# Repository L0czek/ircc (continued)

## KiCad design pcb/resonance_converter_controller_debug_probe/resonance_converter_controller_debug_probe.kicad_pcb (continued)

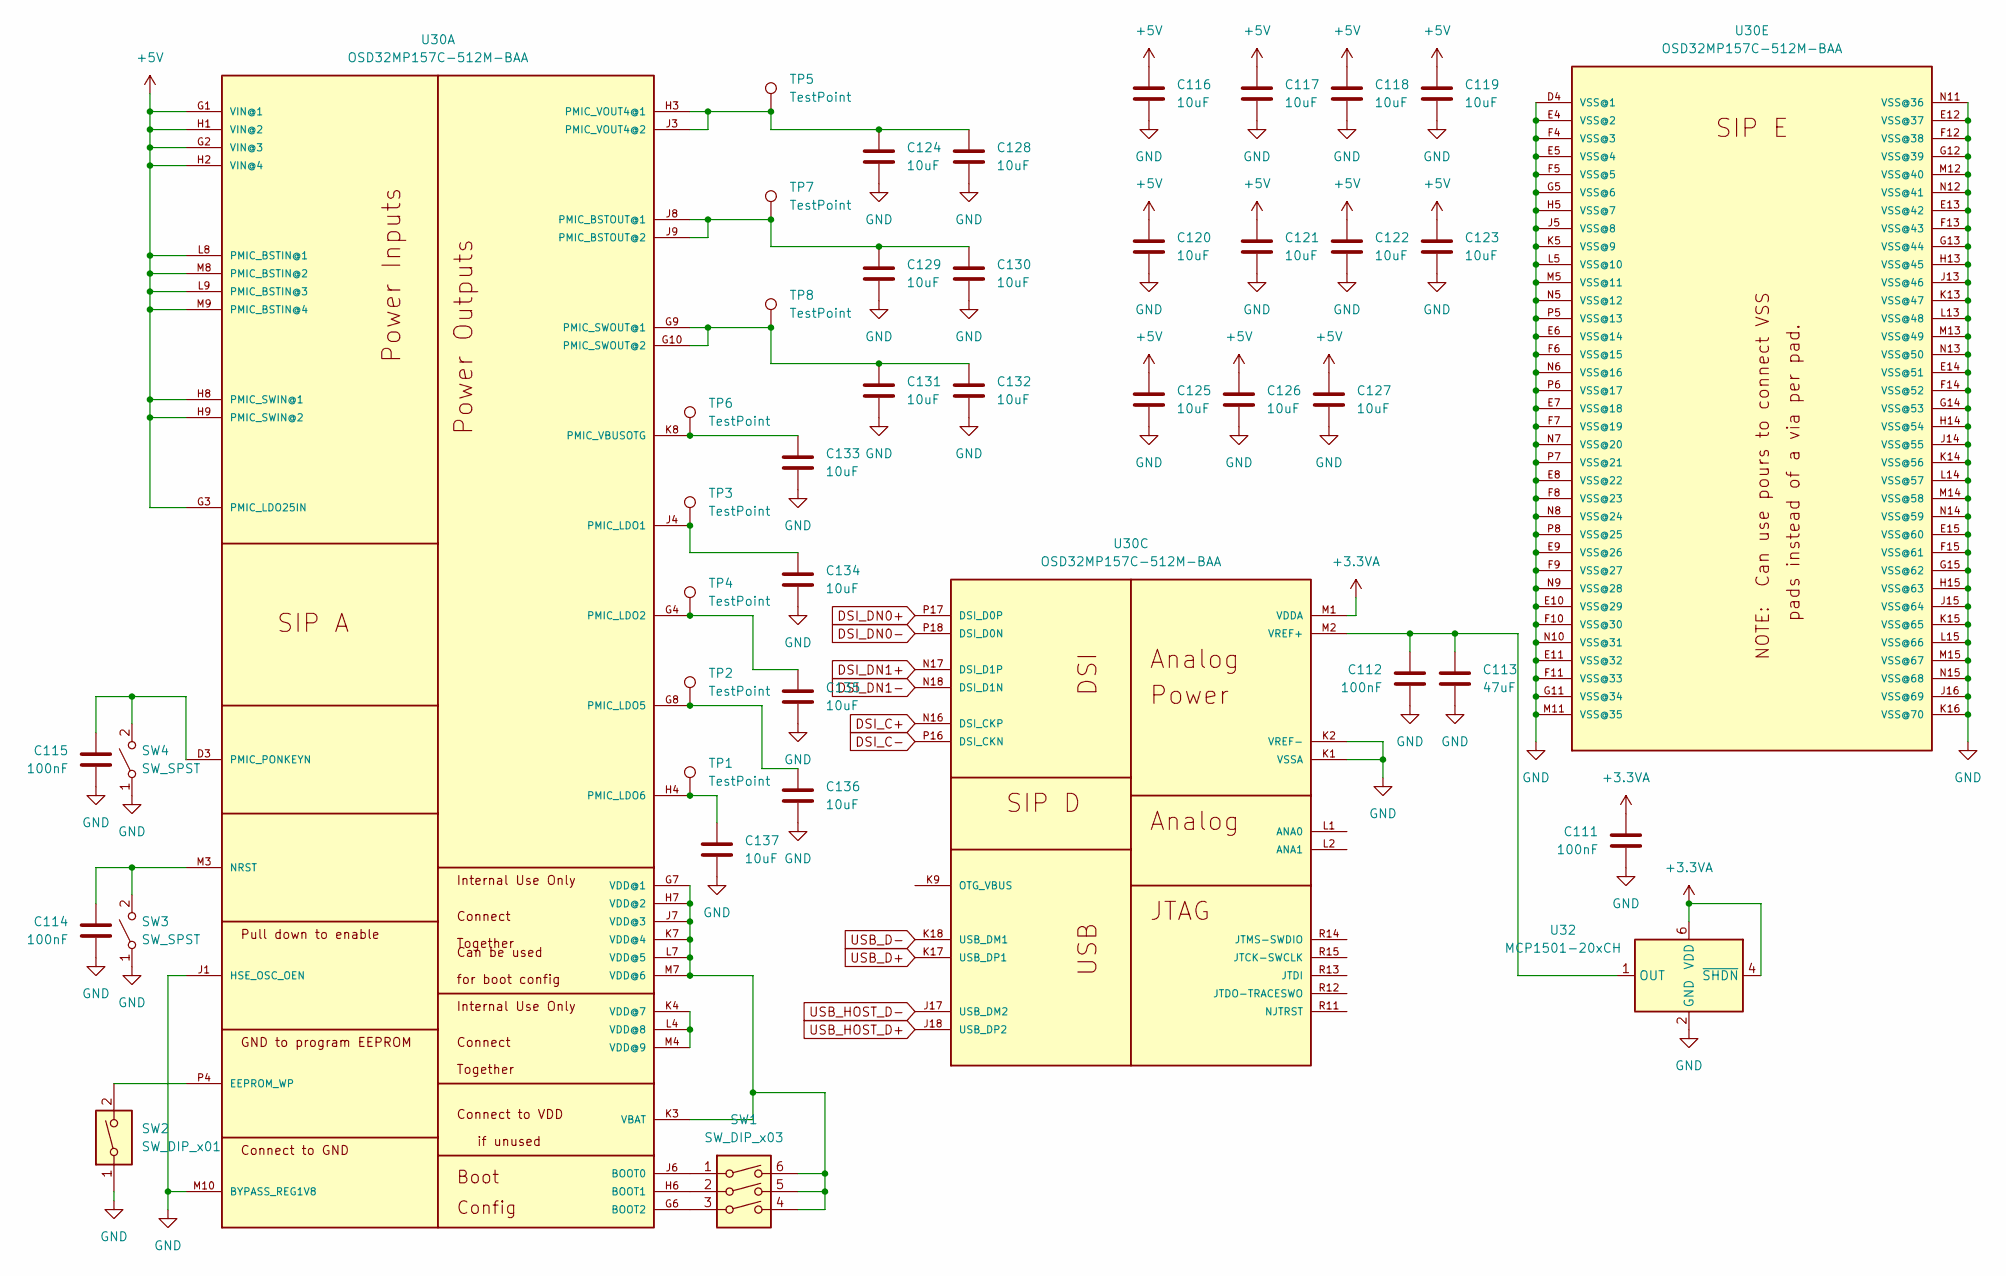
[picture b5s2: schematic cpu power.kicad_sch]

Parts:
C111, C112, C114, C115: 100nF; C_0402_1005Metric
C113: 47uF; C_1206_3216Metric
C116, C117, C118, C119, C120, C121, C122, C123, C124, C125, C126, C127, C128, C129, C130, C131, C132, C133, C134, C135, C136, C137: 10uF; C_0402_1005Metric
SW1: SW_DIP_x03; SW_DIP_SPSTx03_Slide_Omron_A6S-310x_W8.9mm_P2.54mm
SW2: SW_DIP_x01; SW_DIP_SPSTx01_Slide_Omron_A6S-110x_W8.9mm_P2.54mm
SW3, SW4: SW_SPST; SW_SPST_Omron_B3FS-100xP
TP1, TP2, TP3, TP4, TP5, TP6, TP7, TP8: TestPoint; TestPoint_Pad_D1.0mm
U30: OSD32MP157C-512M-BAA; OSD32MP15X-BGA-324
U32: MCP1501-20xCH; SOT-23-6

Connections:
+3.3VA: C111.1, U30.M1 (VDDA), U32.4 (~SHDN), U32.6 (VDD); also elsewhere on the board
+5V: C116.1, C117.1, C118.1, C119.1, C120.1, C121.1, C122.1, C123.1, C125.1, C126.1, C127.1, U30.G1 (VIN@1), U30.G2 (VIN@3), U30.G3 (PMIC_LDO25IN), U30.H1 (VIN@2), U30.H2 (VIN@4), U30.H8 (PMIC_SWIN@1), U30.H9 (PMIC_SWIN@2), U30.L8 (PMIC_BSTIN@1), U30.L9 (PMIC_BSTIN@3), U30.M8 (PMIC_BSTIN@2), U30.M9 (PMIC_BSTIN@4); also elsewhere on the board
DSI_C+: U30.N16 (DSI_CKP); also elsewhere on the board
DSI_C-: U30.P16 (DSI_CKN); also elsewhere on the board
DSI_DN0+: U30.P17 (DSI_D0P); also elsewhere on the board
DSI_DN0-: U30.P18 (DSI_D0N); also elsewhere on the board
DSI_DN1+: U30.N17 (DSI_D1P); also elsewhere on the board
DSI_DN1-: U30.N18 (DSI_D1N); also elsewhere on the board
GND: C111.2, C112.2, C113.2, C114.2, C115.2, C116.2, C117.2, C118.2, C119.2, C120.2, C121.2, C122.2, C123.2, C124.2, C125.2, C126.2, C127.2, C128.2, C129.2, C130.2, C131.2, C132.2, C133.2, C134.2, C135.2, C136.2, C137.2, SW2.1, SW3.1 (A), SW4.1 (A), U30.D4 (VSS@1), U30.E4 (VSS@2), U30.E5 (VSS@4), U30.E6 (VSS@14), U30.E7 (VSS@18), U30.E8 (VSS@22), U30.E9 (VSS@26), U30.E10 (VSS@29), U30.E11 (VSS@32), U30.E12 (VSS@37), U30.E13 (VSS@42), U30.E14 (VSS@51), U30.E15 (VSS@60), U30.F4 (VSS@3), U30.F5 (VSS@5), U30.F6 (VSS@15), U30.F7 (VSS@19), U30.F8 (VSS@23), U30.F9 (VSS@27), U30.F10 (VSS@30), U30.F11 (VSS@33), U30.F12 (VSS@38), U30.F13 (VSS@43), U30.F14 (VSS@52), U30.F15 (VSS@61), U30.G5 (VSS@6), U30.G11 (VSS@34), U30.G12 (VSS@39), U30.G13 (VSS@44), U30.G14 (VSS@53), U30.G15 (VSS@62), U30.H5 (VSS@7), U30.H13 (VSS@45), U30.H14 (VSS@54), U30.H15 (VSS@63), U30.J1 (HSE_OSC_OEN), U30.J5 (VSS@8), U30.J13 (VSS@46), U30.J14 (VSS@55), U30.J15 (VSS@64), U30.J16 (VSS@69), U30.K1 (VSSA), U30.K2 (VREF-), U30.K5 (VSS@9), U30.K13 (VSS@47), U30.K14 (VSS@56), U30.K15 (VSS@65), U30.K16 (VSS@70), U30.L5 (VSS@10), U30.L13 (VSS@48), U30.L14 (VSS@57), U30.L15 (VSS@66), U30.M5 (VSS@11), U30.M10 (BYPASS_REG1V8), U30.M11 (VSS@35), U30.M12 (VSS@40), U30.M13 (VSS@49), U30.M14 (VSS@58), U30.M15 (VSS@67), U30.N5 (VSS@12), U30.N6 (VSS@16), U30.N7 (VSS@20), U30.N8 (VSS@24), U30.N9 (VSS@28), U30.N10 (VSS@31), U30.N11 (VSS@36), U30.N12 (VSS@41), U30.N13 (VSS@50), U30.N14 (VSS@59), U30.N15 (VSS@68), U30.P5 (VSS@13), U30.P6 (VSS@17), U30.P7 (VSS@21), U30.P8 (VSS@25), U32.2 (GND), U32.3 (GND), U32.5 (GND); also elsewhere on the board
unnamed: C114.1, SW3.2 (B), U30.M3 (NRST)
unnamed: C115.1, SW4.2 (B), U30.D3 (PMIC_PONKEYN)
unnamed: SW1.1, U30.J6 (BOOT0)
unnamed: SW1.2, U30.H6 (BOOT1)
unnamed: SW1.3, U30.G6 (BOOT2)
unnamed: SW2.2, U30.P4 (EEPROM_WP)
unnamed: C129.1, C130.1, TP7.1, U30.J8 (PMIC_BSTOUT@1), U30.J9 (PMIC_BSTOUT@2)
unnamed: C134.1, TP3.1, U30.J4 (PMIC_LDO1)
unnamed: C135.1, TP4.1, U30.G4 (PMIC_LDO2)
unnamed: C136.1, TP2.1, U30.G8 (PMIC_LDO5)
unnamed: C137.1, TP1.1, U30.H4 (PMIC_LDO6)
unnamed: C131.1, C132.1, TP8.1, U30.G9 (PMIC_SWOUT@1), U30.G10 (PMIC_SWOUT@2)
unnamed: C133.1, TP6.1, U30.K8 (PMIC_VBUSOTG)
unnamed: C124.1, C128.1, TP5.1, U30.H3 (PMIC_VOUT4@1), U30.J3 (PMIC_VOUT4@2)
unnamed: SW1.4, SW1.5, SW1.6, U30.G7 (VDD@1), U30.H7 (VDD@2), U30.J7 (VDD@3), U30.K3 (VBAT), U30.K7 (VDD@4), U30.L7 (VDD@5), U30.M7 (VDD@6)
unnamed: U30.K4 (VDD@7), U30.L4 (VDD@8), U30.M4 (VDD@9)
unnamed: C112.1, C113.1, U30.M2 (VREF+), U32.1 (OUT)
USB_D+: U30.K17 (USB_DP1); also elsewhere on the board
USB_D-: U30.K18 (USB_DM1); also elsewhere on the board
USB_HOST_D+: U30.J18 (USB_DP2); also elsewhere on the board
USB_HOST_D-: U30.J17 (USB_DM2); also elsewhere on the board

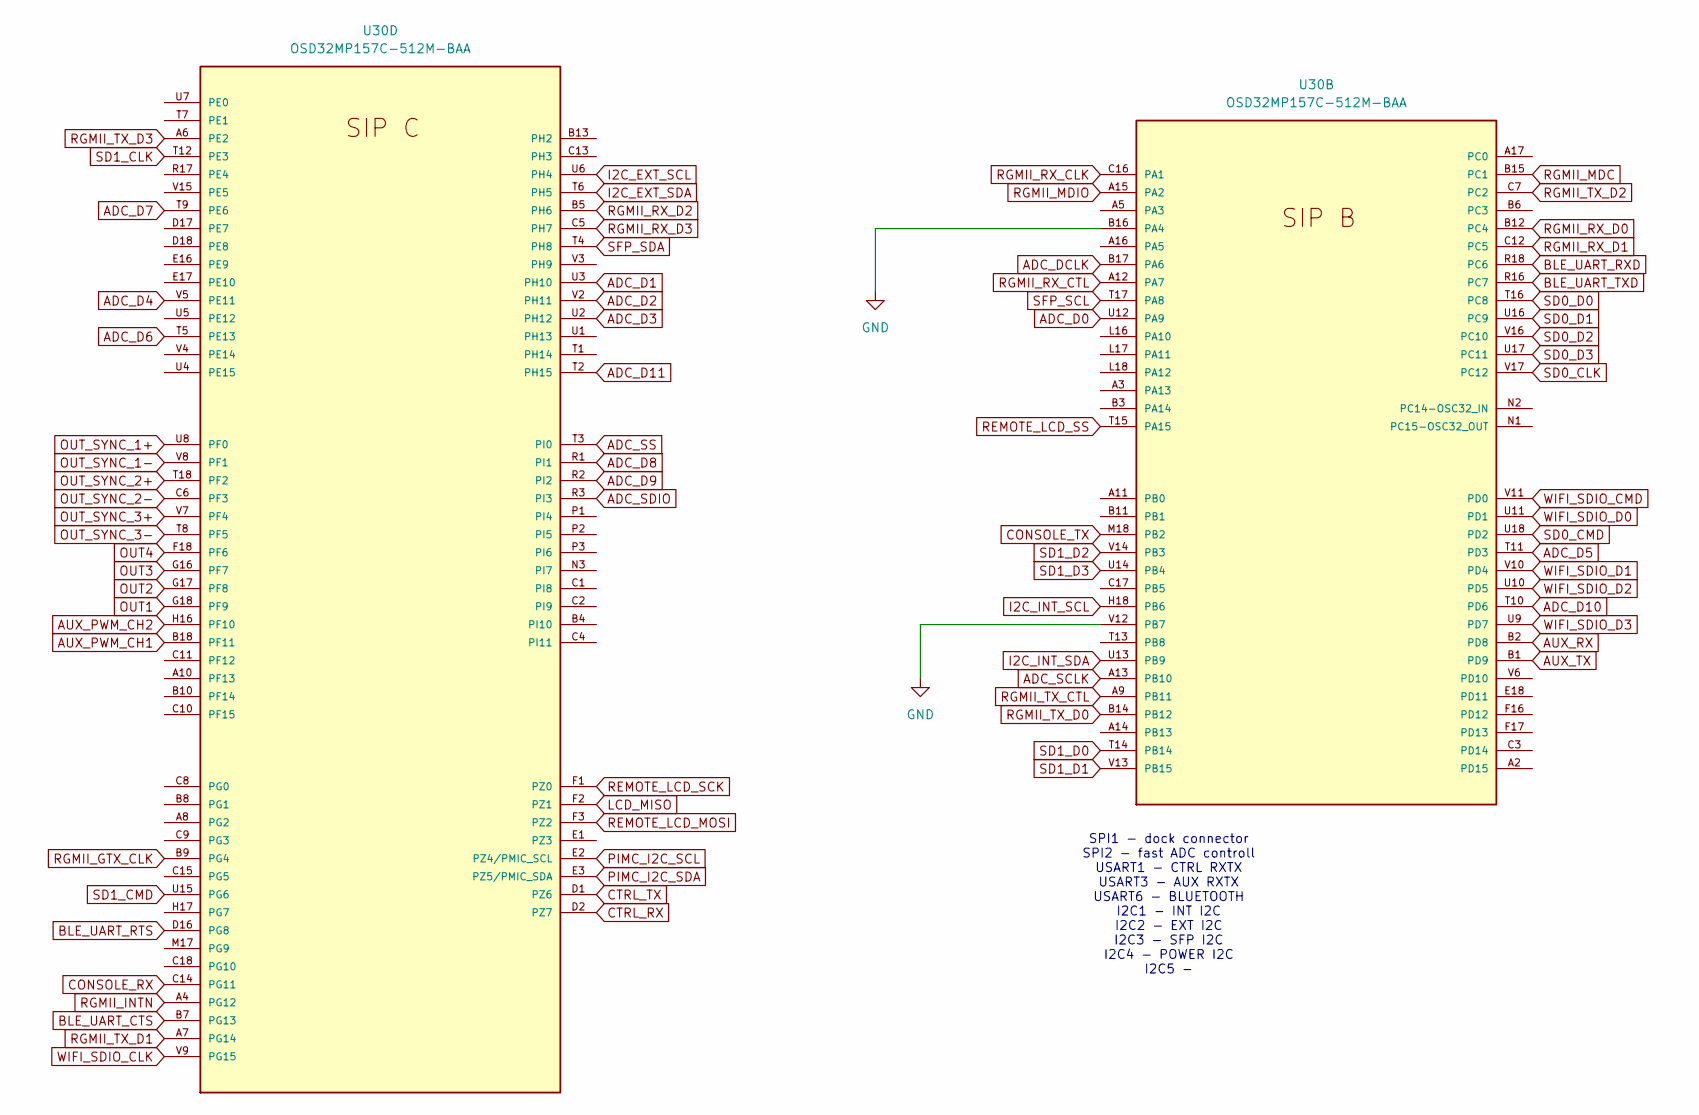
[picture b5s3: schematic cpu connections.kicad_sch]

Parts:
U30: OSD32MP157C-512M-BAA; OSD32MP15X-BGA-324

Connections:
ADC_D0: U30.U12 (PA9); also elsewhere on the board
ADC_D1: U30.U3 (PH10); also elsewhere on the board
ADC_D2: U30.V2 (PH11); also elsewhere on the board
ADC_D3: U30.U2 (PH12); also elsewhere on the board
ADC_D4: U30.V5 (PE11); also elsewhere on the board
ADC_D5: U30.T11 (PD3); also elsewhere on the board
ADC_D6: U30.T5 (PE13); also elsewhere on the board
ADC_D7: U30.T9 (PE6); also elsewhere on the board
ADC_D8: U30.R1 (PI1); also elsewhere on the board
ADC_D9: U30.R2 (PI2); also elsewhere on the board
ADC_D10: U30.T10 (PD6); also elsewhere on the board
ADC_D11: U30.T2 (PH15); also elsewhere on the board
ADC_DCLK: U30.B17 (PA6); also elsewhere on the board
ADC_SCLK: U30.A13 (PB10); also elsewhere on the board
ADC_SDIO: U30.R3 (PI3); also elsewhere on the board
ADC_SS: U30.T3 (PI0); also elsewhere on the board
AUX_PWM_CH1: U30.B18 (PF11); also elsewhere on the board
AUX_PWM_CH2: U30.H16 (PF10); also elsewhere on the board
AUX_RX: U30.B2 (PD8); also elsewhere on the board
AUX_TX: U30.B1 (PD9); also elsewhere on the board
BLE_UART_CTS: U30.B7 (PG13); also elsewhere on the board
BLE_UART_RTS: U30.D16 (PG8); also elsewhere on the board
BLE_UART_RXD: U30.R18 (PC6); also elsewhere on the board
BLE_UART_TXD: U30.R16 (PC7); also elsewhere on the board
CONSOLE_RX: U30.C14 (PG11); also elsewhere on the board
CONSOLE_TX: U30.M18 (PB2); also elsewhere on the board
CTRL_RX: U30.D2 (PZ7); also elsewhere on the board
CTRL_TX: U30.D1 (PZ6); also elsewhere on the board
GND: U30.B16 (PA4), U30.V12 (PB7); also elsewhere on the board
I2C_EXT_SCL: U30.U6 (PH4); also elsewhere on the board
I2C_EXT_SDA: U30.T6 (PH5); also elsewhere on the board
I2C_INT_SCL: U30.H18 (PB6); also elsewhere on the board
I2C_INT_SDA: U30.U13 (PB9); also elsewhere on the board
LCD_MISO: U30.F2 (PZ1)
OUT1: U30.G18 (PF9); also elsewhere on the board
OUT2: U30.G17 (PF8); also elsewhere on the board
OUT3: U30.G16 (PF7); also elsewhere on the board
OUT4: U30.F18 (PF6); also elsewhere on the board
OUT_SYNC_1+: U30.U8 (PF0); also elsewhere on the board
OUT_SYNC_1-: U30.V8 (PF1); also elsewhere on the board
OUT_SYNC_2+: U30.T18 (PF2); also elsewhere on the board
OUT_SYNC_2-: U30.C6 (PF3); also elsewhere on the board
OUT_SYNC_3+: U30.V7 (PF4); also elsewhere on the board
OUT_SYNC_3-: U30.T8 (PF5); also elsewhere on the board
PIMC_I2C_SCL: U30.E2 (PZ4/PMIC_SCL)
PIMC_I2C_SDA: U30.E3 (PZ5/PMIC_SDA)
REMOTE_LCD_MOSI: U30.F3 (PZ2)
REMOTE_LCD_SCK: U30.F1 (PZ0)
REMOTE_LCD_SS: U30.T15 (PA15)
RGMII_GTX_CLK: U30.B9 (PG4); also elsewhere on the board
RGMII_INTN: U30.A4 (PG12); also elsewhere on the board
RGMII_MDC: U30.B15 (PC1); also elsewhere on the board
RGMII_MDIO: U30.A15 (PA2); also elsewhere on the board
RGMII_RX_CLK: U30.C16 (PA1); also elsewhere on the board
RGMII_RX_CTL: U30.A12 (PA7); also elsewhere on the board
RGMII_RX_D0: U30.B12 (PC4); also elsewhere on the board
RGMII_RX_D1: U30.C12 (PC5); also elsewhere on the board
RGMII_RX_D2: U30.B5 (PH6); also elsewhere on the board
RGMII_RX_D3: U30.C5 (PH7); also elsewhere on the board
RGMII_TX_CTL: U30.A9 (PB11); also elsewhere on the board
RGMII_TX_D0: U30.B14 (PB12); also elsewhere on the board
RGMII_TX_D1: U30.A7 (PG14); also elsewhere on the board
RGMII_TX_D2: U30.C7 (PC2); also elsewhere on the board
RGMII_TX_D3: U30.A6 (PE2); also elsewhere on the board
SD0_CLK: U30.V17 (PC12); also elsewhere on the board
SD0_CMD: U30.U18 (PD2); also elsewhere on the board
SD0_D0: U30.T16 (PC8); also elsewhere on the board
SD0_D1: U30.U16 (PC9); also elsewhere on the board
SD0_D2: U30.V16 (PC10); also elsewhere on the board
SD0_D3: U30.U17 (PC11); also elsewhere on the board
SD1_CLK: U30.T12 (PE3); also elsewhere on the board
SD1_CMD: U30.U15 (PG6); also elsewhere on the board
SD1_D0: U30.T14 (PB14); also elsewhere on the board
SD1_D1: U30.V13 (PB15); also elsewhere on the board
SD1_D2: U30.V14 (PB3); also elsewhere on the board
SD1_D3: U30.U14 (PB4); also elsewhere on the board
SFP_SCL: U30.T17 (PA8); also elsewhere on the board
SFP_SDA: U30.T4 (PH8); also elsewhere on the board
WIFI_SDIO_CLK: U30.V9 (PG15); also elsewhere on the board
WIFI_SDIO_CMD: U30.V11 (PD0); also elsewhere on the board
WIFI_SDIO_D0: U30.U11 (PD1); also elsewhere on the board
WIFI_SDIO_D1: U30.V10 (PD4); also elsewhere on the board
WIFI_SDIO_D2: U30.U10 (PD5); also elsewhere on the board
WIFI_SDIO_D3: U30.U9 (PD7); also elsewhere on the board

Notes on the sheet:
SPI1 - dock connector SPI2 - fast ADC controll USART1 - CTRL RXTX USART3 - AUX RXTX USART6 - BLUETOOTH I2C1 - INT I2C I2C2 - EXT I2C I2C3 - SFP I2C I2C4 - POWER I2C I2C5 -

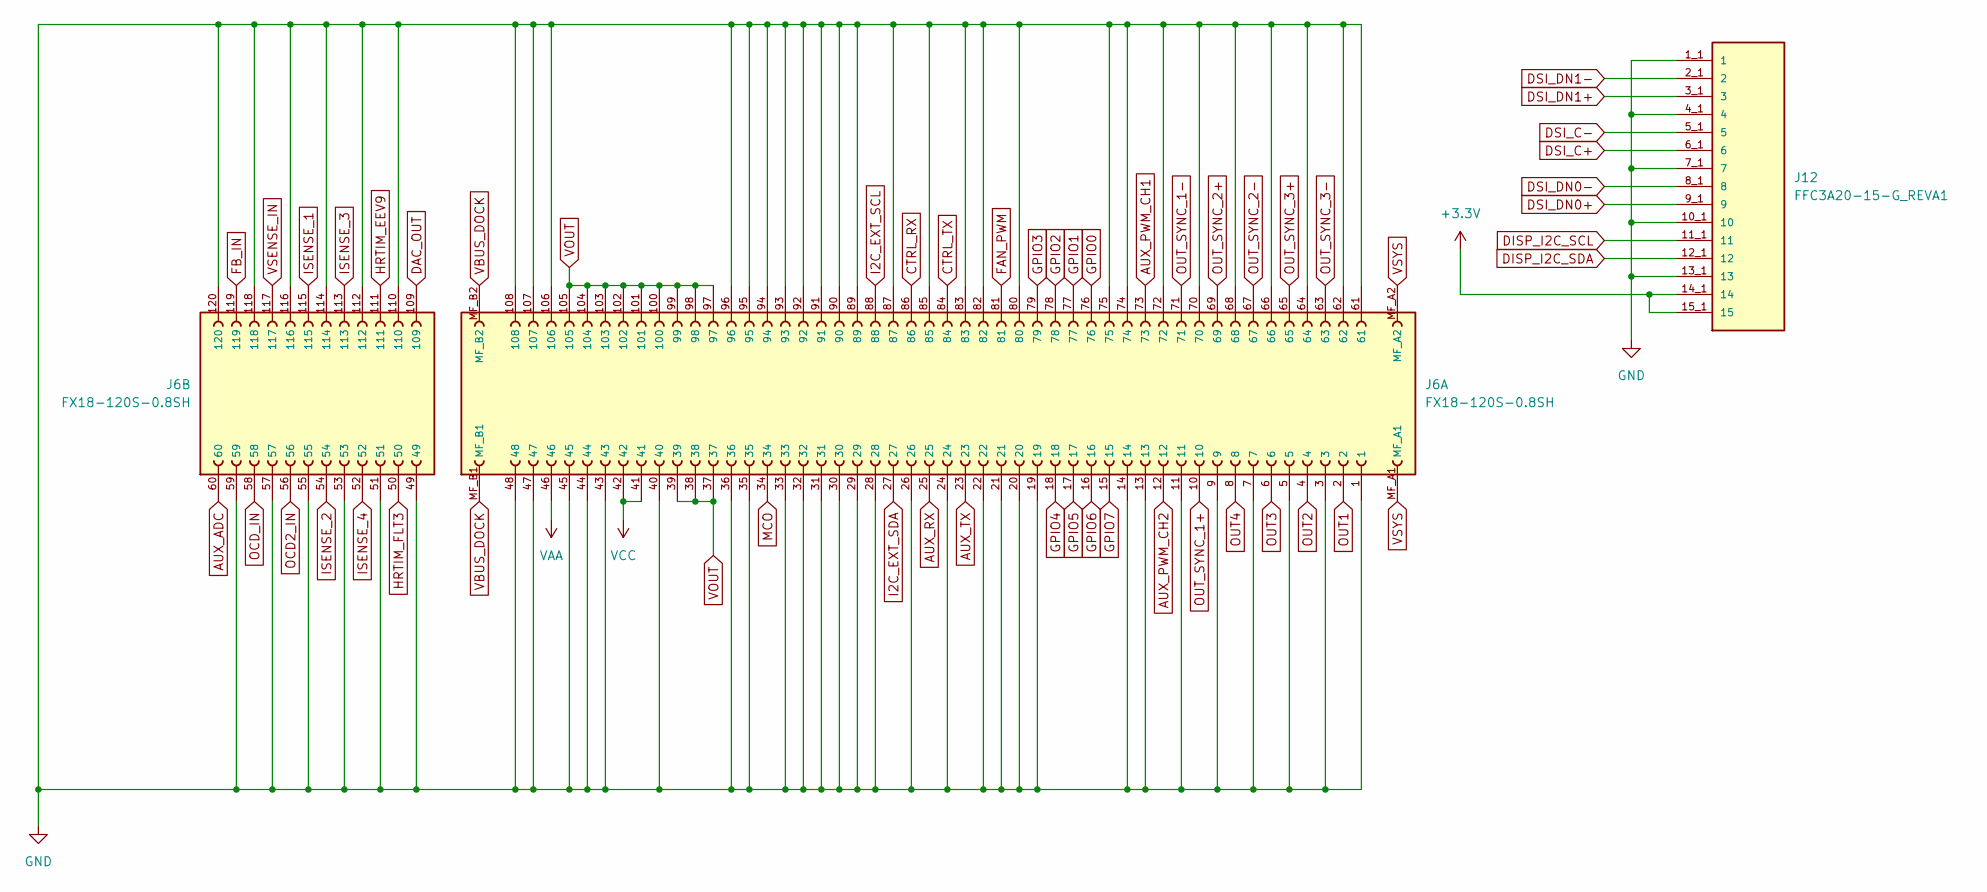
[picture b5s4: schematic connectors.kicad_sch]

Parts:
J6: FX18-120S-0.8SH; HIROSE_FX18-120S-0.8SH; PARTREV 1
J12: FFC3A20-15-G_REVA1; GCT_FFC3A20-15-G_REVA1; PARTREV A1

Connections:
+3.3V: J12.14_1 (14), J12.14_2 (14), J12.15_1 (15), J12.15_2 (15); also elsewhere on the board
AUX_ADC: J6.60; also elsewhere on the board
AUX_PWM_CH1: J6.73; also elsewhere on the board
AUX_PWM_CH2: J6.12; also elsewhere on the board
AUX_RX: J6.25; also elsewhere on the board
AUX_TX: J6.23; also elsewhere on the board
CTRL_RX: J6.86; also elsewhere on the board
CTRL_TX: J6.84; also elsewhere on the board
DAC_OUT: J6.109; also elsewhere on the board
DISP_I2C_SCL: J12.11_1 (11), J12.11_2 (11)
DISP_I2C_SDA: J12.12_1 (12), J12.12_2 (12)
DSI_C+: J12.6_1 (6), J12.6_2 (6); also elsewhere on the board
DSI_C-: J12.5_1 (5), J12.5_2 (5); also elsewhere on the board
DSI_DN0+: J12.9_1 (9), J12.9_2 (9); also elsewhere on the board
DSI_DN0-: J12.8_1 (8), J12.8_2 (8); also elsewhere on the board
DSI_DN1+: J12.3_1 (3), J12.3_2 (3); also elsewhere on the board
DSI_DN1-: J12.2_1 (2), J12.2_2 (2); also elsewhere on the board
FAN_PWM: J6.81
FB_IN: J6.119
GND: J6.1, J6.3, J6.5, J6.7, J6.9, J6.11, J6.13, J6.14, J6.19, J6.20, J6.21, J6.22, J6.24, J6.26, J6.28, J6.29, J6.30, J6.31, J6.32, J6.33, J6.35, J6.36, J6.40, J6.43, J6.44, J6.45, J6.47, J6.48, J6.49, J6.51, J6.53, J6.55, J6.57, J6.59, J6.61, J6.62, J6.64, J6.66, J6.68, J6.70, J6.72, J6.74, J6.75, J6.80, J6.82, J6.83, J6.85, J6.87, J6.89, J6.90, J6.91, J6.92, J6.93, J6.94, J6.95, J6.96, J6.106, J6.107, J6.108, J6.110, J6.112, J6.114, J6.116, J6.118, J6.120, J12.1_1 (1), J12.1_2 (1), J12.4_1 (4), J12.4_2 (4), J12.7_1 (7), J12.7_2 (7), J12.10_1 (10), J12.10_2 (10), J12.13_1 (13), J12.13_2 (13); also elsewhere on the board
GPIO0: J6.76
GPIO1: J6.77
GPIO2: J6.78
GPIO3: J6.79
GPIO4: J6.18
GPIO5: J6.17
GPIO6: J6.16
GPIO7: J6.15
HRTIM_EEV9: J6.111
HRTIM_FLT3: J6.50
I2C_EXT_SCL: J6.88; also elsewhere on the board
I2C_EXT_SDA: J6.27; also elsewhere on the board
ISENSE_1: J6.115; also elsewhere on the board
ISENSE_2: J6.54; also elsewhere on the board
ISENSE_3: J6.113; also elsewhere on the board
ISENSE_4: J6.52; also elsewhere on the board
MCO: J6.34
OCD2_IN: J6.56; also elsewhere on the board
OCD_IN: J6.58; also elsewhere on the board
OUT1: J6.2; also elsewhere on the board
OUT2: J6.4; also elsewhere on the board
OUT3: J6.6; also elsewhere on the board
OUT4: J6.8; also elsewhere on the board
OUT_SYNC_1+: J6.10; also elsewhere on the board
OUT_SYNC_1-: J6.71; also elsewhere on the board
OUT_SYNC_2+: J6.69; also elsewhere on the board
OUT_SYNC_2-: J6.67; also elsewhere on the board
OUT_SYNC_3+: J6.65; also elsewhere on the board
OUT_SYNC_3-: J6.63; also elsewhere on the board
VAA: J6.46
VBUS_DOCK: J6.MF_B1, J6.MF_B2; also elsewhere on the board
VCC: J6.41, J6.42
VOUT: J6.37, J6.38, J6.39, J6.97, J6.98, J6.99, J6.100, J6.101, J6.102, J6.103, J6.104, J6.105
VSENSE_IN: J6.117; also elsewhere on the board
VSYS: J6.MF_A1, J6.MF_A2; also elsewhere on the board

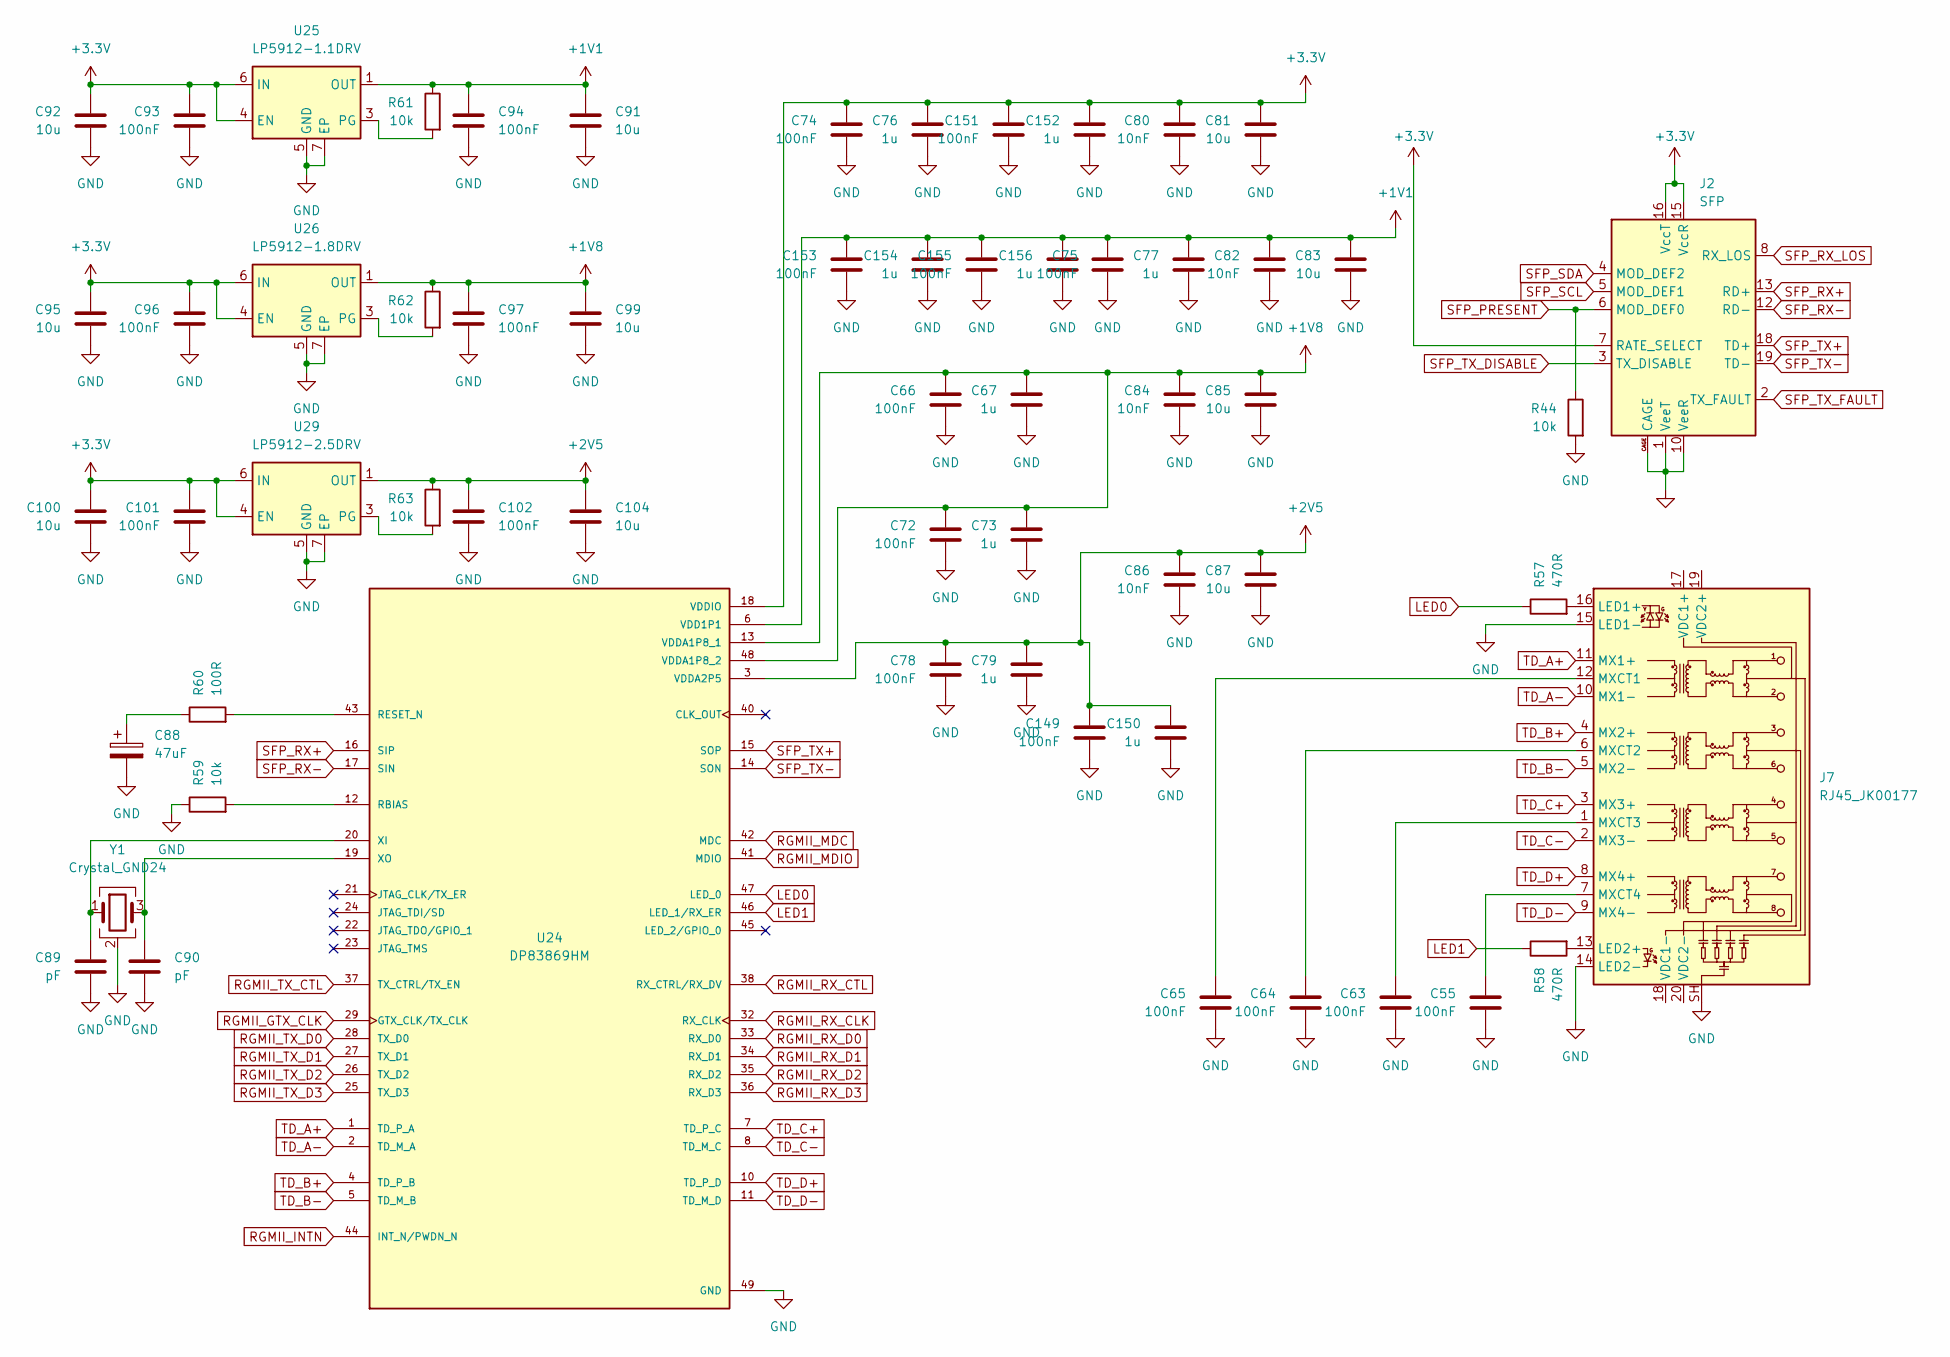
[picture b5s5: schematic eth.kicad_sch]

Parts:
C55, C63, C64, C65, C66, C72, C74, C75, C78, C93, C94, C96, C97, C101, C102, C149, C151, C153, C155: 100nF; C_0402_1005Metric
C67, C73, C76, C77, C79, C150, C152, C154, C156: 1u; C_0402_1005Metric
C80, C82, C84, C86: 10nF; C_0402_1005Metric
C81, C83, C85, C87, C91, C92, C95, C99, C100, C104: 10u; C_0805_2012Metric
C88: 47uF; C_1206_3216Metric
C89, C90: pF; C_0402_1005Metric
J2: SFP; Connector_SFP_and_Cage
J7: RJ45_JK00177; RJ45_Pulse_JK00177NL_Horizontal
R44, R59, R61, R62, R63: 10k; R_0402_1005Metric
R57, R58: 470R; R_0402_1005Metric
R60: 100R; R_0402_1005Metric
U24: DP83869HM; QFN50P700X700X100-49N; PARTREV A
U25: LP5912-1.1DRV; WSON-6-1EP_2x2mm_P0.65mm_EP1x1.6mm_ThermalVias
U26: LP5912-1.8DRV; WSON-6-1EP_2x2mm_P0.65mm_EP1x1.6mm_ThermalVias
U29: LP5912-2.5DRV; WSON-6-1EP_2x2mm_P0.65mm_EP1x1.6mm_ThermalVias
Y1: Crystal_GND24; Crystal_SMD_3225-4Pin_3.2x2.5mm

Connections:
+1V1: C75.1, C77.1, C82.1, C83.1, C91.1, C94.1, C153.1, C154.1, C155.1, C156.1, R61.1, U24.6 (VDD1P1), U24.31 (VDD1P1), U24.39 (VDD1P1), U25.1 (OUT)
+1V8: C66.1, C67.1, C72.1, C73.1, C84.1, C85.1, C97.1, C99.1, R62.1, U24.13 (VDDA1P8_1), U24.48 (VDDA1P8_2), U26.1 (OUT); also elsewhere on the board
+2V5: C78.1, C79.1, C86.1, C87.1, C102.1, C104.1, C149.1, C150.1, R63.1, U24.3 (VDDA2P5), U24.9 (VDDA2P5), U29.1 (OUT)
+3.3V: C74.1, C76.1, C80.1, C81.1, C92.1, C93.1, C95.1, C96.1, C100.1, C101.1, C151.1, C152.1, J2.7 (RATE_SELECT), J2.15 (VccR), J2.16 (VccT), U24.18 (VDDIO), U24.30 (VDDIO), U25.4 (EN), U25.6 (IN), U26.4 (EN), U26.6 (IN), U29.4 (EN), U29.6 (IN); also elsewhere on the board
GND: C55.2, C63.2, C64.2, C65.2, C66.2, C67.2, C72.2, C73.2, C74.2, C75.2, C76.2, C77.2, C78.2, C79.2, C80.2, C81.2, C82.2, C83.2, C84.2, C85.2, C86.2, C87.2, C88.2, C89.2, C90.2, C91.2, C92.2, C93.2, C94.2, C95.2, C96.2, C97.2, C99.2, C100.2, C101.2, C102.2, C104.2, C149.2, C150.2, C151.2, C152.2, C153.2, C154.2, C155.2, C156.2, J2.1 (VeeT), J2.9 (VeeR), J2.10 (VeeR), J2.11 (VeeR), J2.14 (VeeR), J2.17 (VeeT), J2.20 (VeeT), J2.CAGE, J7.14 (LED2-), J7.15 (LED1-), J7.SH, R44.2, R59.1, U24.49 (GND), U25.5 (GND), U25.7 (EP), U26.5 (GND), U26.7 (EP), U29.5 (GND), U29.7 (EP), Y1.2 (G), Y1.4 (G); also elsewhere on the board
LED0: R57.1, U24.47 (LED_0)
LED1: R58.1, U24.46 (LED_1/RX_ER)
unnamed: C88.1, R60.1
unnamed: J7.16 (LED1+), R57.2
unnamed: J7.13 (LED2+), R58.2
unnamed: C65.1, J7.12 (MXCT1)
unnamed: C64.1, J7.6 (MXCT2)
unnamed: C63.1, J7.1 (MXCT3)
unnamed: C55.1, J7.7 (MXCT4)
unnamed: R59.2, U24.12 (RBIAS)
unnamed: R60.2, U24.43 (RESET_N)
unnamed: C89.1, U24.20 (XI), Y1.1
unnamed: C90.1, U24.19 (XO), Y1.3
unnamed: R61.2, U25.3 (PG)
unnamed: R62.2, U26.3 (PG)
unnamed: R63.2, U29.3 (PG)
RGMII_GTX_CLK: U24.29 (GTX_CLK/TX_CLK); also elsewhere on the board
RGMII_INTN: U24.44 (INT_N/PWDN_N); also elsewhere on the board
RGMII_MDC: U24.42 (MDC); also elsewhere on the board
RGMII_MDIO: U24.41 (MDIO); also elsewhere on the board
RGMII_RX_CLK: U24.32 (RX_CLK); also elsewhere on the board
RGMII_RX_CTL: U24.38 (RX_CTRL/RX_DV); also elsewhere on the board
RGMII_RX_D0: U24.33 (RX_D0); also elsewhere on the board
RGMII_RX_D1: U24.34 (RX_D1); also elsewhere on the board
RGMII_RX_D2: U24.35 (RX_D2); also elsewhere on the board
RGMII_RX_D3: U24.36 (RX_D3); also elsewhere on the board
RGMII_TX_CTL: U24.37 (TX_CTRL/TX_EN); also elsewhere on the board
RGMII_TX_D0: U24.28 (TX_D0); also elsewhere on the board
RGMII_TX_D1: U24.27 (TX_D1); also elsewhere on the board
RGMII_TX_D2: U24.26 (TX_D2); also elsewhere on the board
RGMII_TX_D3: U24.25 (TX_D3); also elsewhere on the board
SFP_PRESENT: J2.6 (MOD_DEF0), R44.1
SFP_RX+: J2.13 (RD+), U24.16 (SIP)
SFP_RX-: J2.12 (RD-), U24.17 (SIN)
SFP_RX_LOS: J2.8 (RX_LOS)
SFP_SCL: J2.5 (MOD_DEF1); also elsewhere on the board
SFP_SDA: J2.4 (MOD_DEF2); also elsewhere on the board
SFP_TX+: J2.18 (TD+), U24.15 (SOP)
SFP_TX-: J2.19 (TD-), U24.14 (SON)
SFP_TX_DISABLE: J2.3 (TX_DISABLE)
SFP_TX_FAULT: J2.2 (TX_FAULT)
TD_A+: J7.11 (MX1+), U24.1 (TD_P_A)
TD_A-: J7.10 (MX1-), U24.2 (TD_M_A)
TD_B+: J7.4 (MX2+), U24.4 (TD_P_B)
TD_B-: J7.5 (MX2-), U24.5 (TD_M_B)
TD_C+: J7.3 (MX3+), U24.7 (TD_P_C)
TD_C-: J7.2 (MX3-), U24.8 (TD_M_C)
TD_D+: J7.8 (MX4+), U24.10 (TD_P_D)
TD_D-: J7.9 (MX4-), U24.11 (TD_M_D)

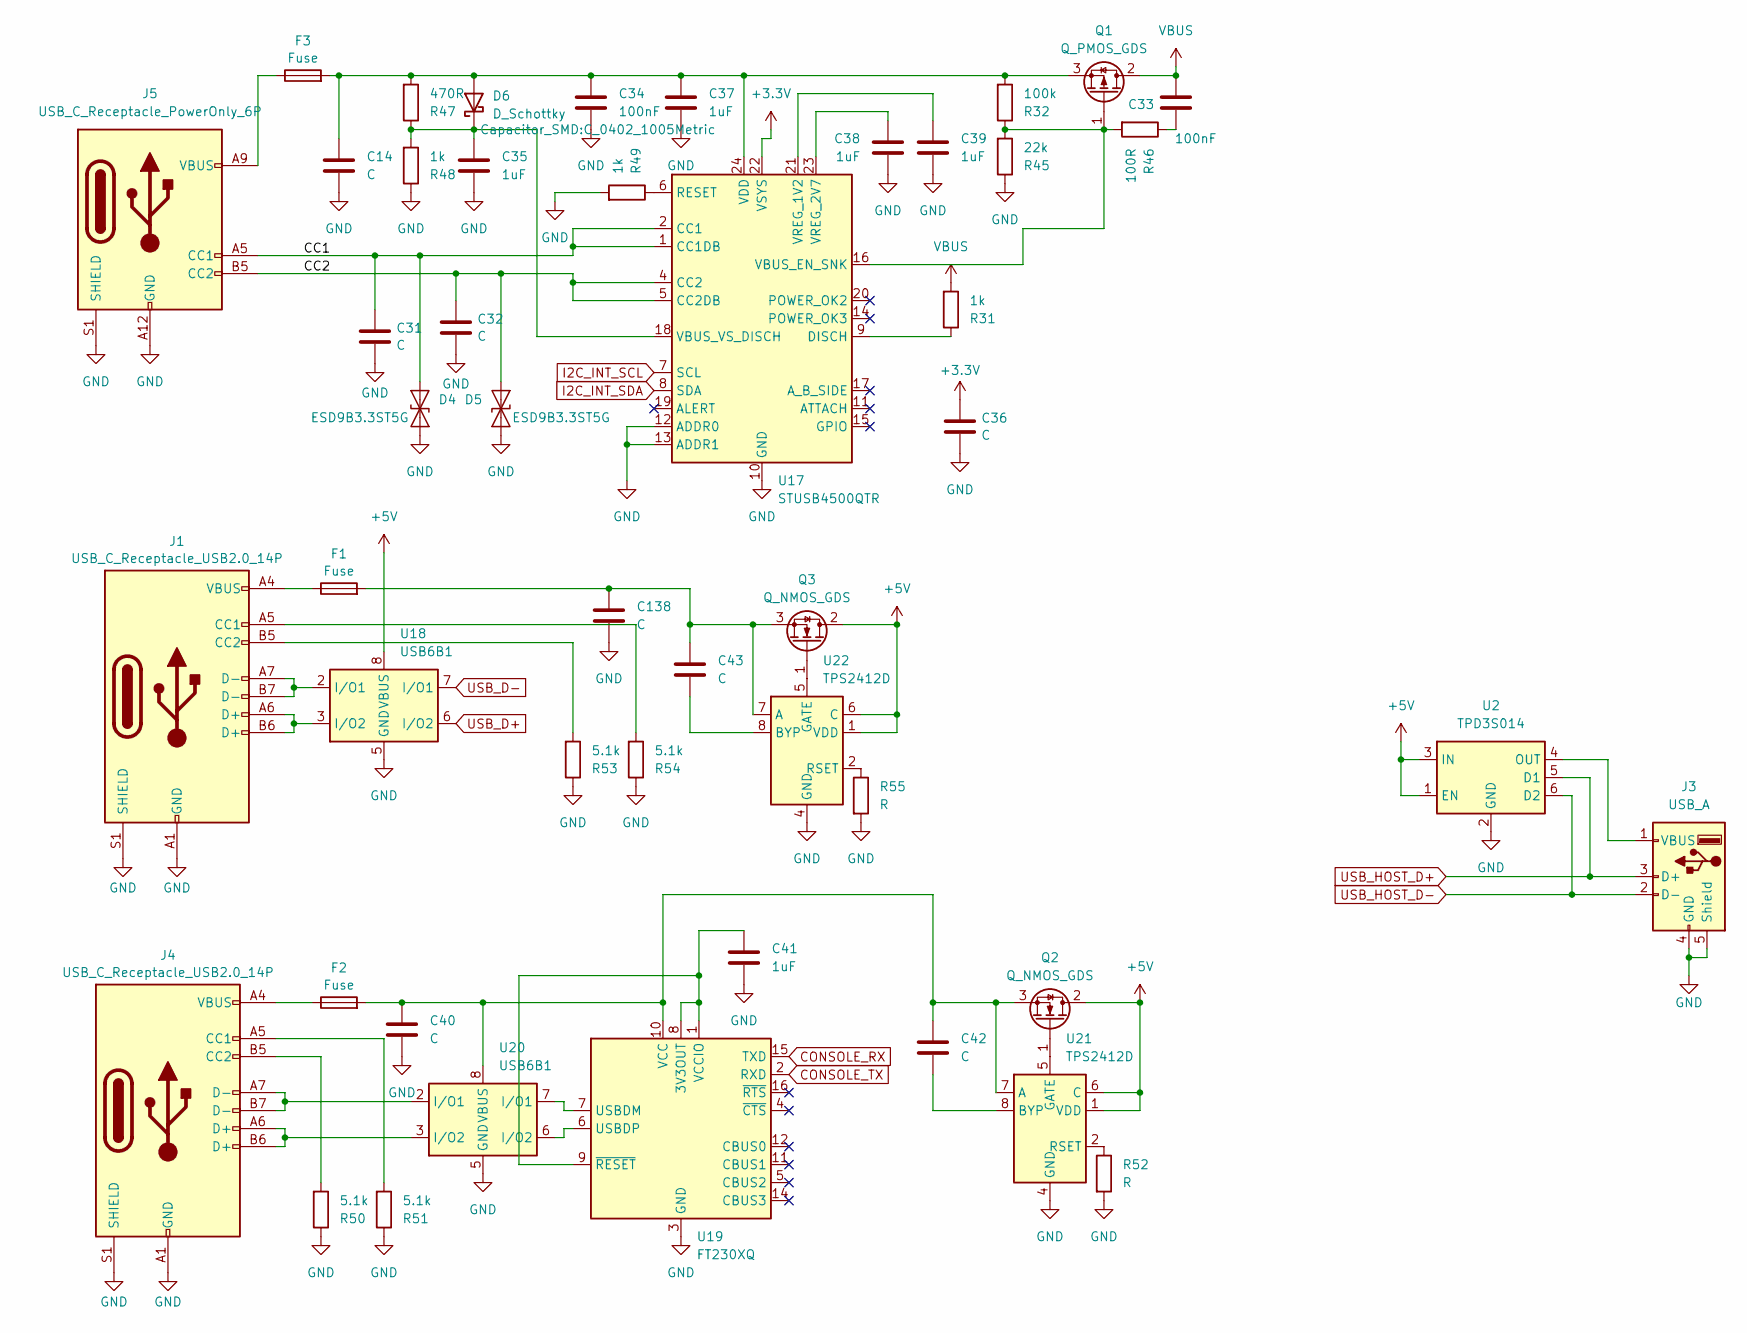
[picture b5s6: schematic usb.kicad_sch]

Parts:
C14, C40, C138: C; C_1206_3216Metric
C31, C32, C36: C; C_0402_1005Metric
C33: 100nF; C_0805_2012Metric
C34: 100nF; C_0402_1005Metric
C35, C37, C38, C39, C41: 1uF; C_0805_2012Metric
C42, C43: C; C_0805_2012Metric
D4, D5: ESD9B3.3ST5G; D_SOD-923
D6: D_Schottky; D_MiniMELF
F1, F2, F3: Fuse; Fuse_0805_2012Metric
J1, J4: USB_C_Receptacle_USB2.0_14P; USB_C_Receptacle_G-Switch_GT-USB-7010ASV
J3: USB_A; USB_A_Molex_67643_Horizontal
J5: USB_C_Receptacle_PowerOnly_6P; USB_C_Receptacle_GCT_USB4125-xx-x-0190_6P_TopMnt_Horizontal
Q1: Q_PMOS_GDS; TO-252-2
Q2, Q3: Q_NMOS_GDS; TO-252-2
R31, R48, R49: 1k; R_0402_1005Metric
R32: 100k; R_0402_1005Metric
R45: 22k; R_0402_1005Metric
R46: 100R; R_0402_1005Metric
R47: 470R; R_0402_1005Metric
R50, R51, R53, R54: 5.1k; R_0402_1005Metric
R52, R55: R; R_0402_1005Metric
U2: TPD3S014; SOT-23-6
U17: STUSB4500QTR; QFN-24-1EP_4x4mm_P0.5mm_EP2.7x2.7mm
U18, U20: USB6B1; SOIC-8_3.9x4.9mm_P1.27mm
U19: FT230XQ; QFN-16-1EP_4x4mm_P0.65mm_EP2.1x2.1mm
U21, U22: TPS2412D; TSSOP-8_4.4x3mm_P0.65mm

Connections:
+3.3V: C36.1, U17.22 (VSYS); also elsewhere on the board
+5V: Q2.2 (D), Q3.2 (D), U2.1 (EN), U2.3 (IN), U18.1 (VBUS), U18.8 (VBUS), U21.1 (VDD), U21.6 (C), U22.1 (VDD), U22.6 (C); also elsewhere on the board
/USB/CC1: C31.1, D4.2 (A2), J5.A5 (CC1), U17.1 (CC1DB), U17.2 (CC1)
/USB/CC2: C32.1, D5.2 (A2), J5.B5 (CC2), U17.4 (CC2), U17.5 (CC2DB)
CONSOLE_RX: U19.15 (TXD); also elsewhere on the board
CONSOLE_TX: U19.2 (RXD); also elsewhere on the board
GND: C14.2, C31.2, C32.2, C34.2, C35.2, C36.2, C37.2, C38.2, C39.2, C40.2, C41.2, C138.2, D4.1 (A1), D5.1 (A1), J1.A1 (GND), J1.A12 (GND), J1.B1 (GND), J1.B12 (GND), J1.S1 (SHIELD), J3.4 (GND), J3.5 (Shield), J4.A1 (GND), J4.A12 (GND), J4.B1 (GND), J4.B12 (GND), J4.S1 (SHIELD), J5.A12 (GND), J5.B12 (GND), J5.S1 (SHIELD), R45.1, R48.1, R49.2, R50.1, R51.1, R52.2, R53.1, R54.1, R55.2, U2.2 (GND), U17.10 (GND), U17.12 (ADDR0), U17.13 (ADDR1), U17.25 (GND), U18.4 (GND), U18.5 (GND), U19.3 (GND), U19.13 (GND), U19.17 (GND), U20.4 (GND), U20.5 (GND), U21.3 (GND), U21.4 (GND), U22.3 (GND), U22.4 (GND); also elsewhere on the board
I2C_INT_SCL: U17.7 (SCL); also elsewhere on the board
I2C_INT_SDA: U17.8 (SDA); also elsewhere on the board
unnamed: C33.2, R46.1
unnamed: C14.1, C34.1, C37.1, D6.2 (A), F3.2, Q1.3 (S), R32.2, R47.2, U17.24 (VDD)
unnamed: C35.1, D6.1 (K), R47.1, R48.2, U17.18 (VBUS_VS_DISCH)
unnamed: F1.1, J1.A4 (VBUS), J1.A9 (VBUS), J1.B4 (VBUS), J1.B9 (VBUS)
unnamed: F2.1, J4.A4 (VBUS), J4.A9 (VBUS), J4.B4 (VBUS), J4.B9 (VBUS)
unnamed: F3.1, J5.A9 (VBUS), J5.B9 (VBUS)
unnamed: J1.A5 (CC1), R54.2
unnamed: J1.B5 (CC2), R53.2
unnamed: J1.A6 (D+), J1.B6 (D+), U18.3 (I/O2)
unnamed: J1.A7 (D-), J1.B7 (D-), U18.2 (I/O1)
unnamed: J3.1 (VBUS), U2.4 (OUT)
unnamed: J4.A5 (CC1), R51.2
unnamed: J4.B5 (CC2), R50.2
unnamed: J4.A6 (D+), J4.B6 (D+), U20.3 (I/O2)
unnamed: J4.A7 (D-), J4.B7 (D-), U20.2 (I/O1)
unnamed: Q1.1 (G), R32.1, R45.2, R46.2, U17.16 (VBUS_EN_SNK)
unnamed: Q2.1 (G), U21.5 (GATE)
unnamed: C40.1, C42.1, F2.2, Q2.3 (S), U19.10 (VCC), U20.1 (VBUS), U20.8 (VBUS), U21.7 (A)
unnamed: Q3.1 (G), U22.5 (GATE)
unnamed: C43.1, C138.1, F1.2, Q3.3 (S), U22.7 (A)
unnamed: R31.1, U17.9 (DISCH)
unnamed: R49.1, U17.6 (RESET)
unnamed: C39.1, U17.21 (VREG_1V2)
unnamed: C38.1, U17.23 (VREG_2V7)
unnamed: C41.1, U19.1 (VCCIO), U19.8 (3V3OUT), U19.9 (~RESET)
unnamed: U19.7 (USBDM), U20.7 (I/O1)
unnamed: U19.6 (USBDP), U20.6 (I/O2)
unnamed: C42.2, U21.8 (BYP)
unnamed: R52.1, U21.2 (RSET)
unnamed: C43.2, U22.8 (BYP)
unnamed: R55.1, U22.2 (RSET)
USB_D+: U18.6 (I/O2); also elsewhere on the board
USB_D-: U18.7 (I/O1); also elsewhere on the board
USB_HOST_D+: J3.3 (D+), U2.5 (D1); also elsewhere on the board
USB_HOST_D-: J3.2 (D-), U2.6 (D2); also elsewhere on the board
VBUS: C33.1, Q1.2 (D), R31.2; also elsewhere on the board
